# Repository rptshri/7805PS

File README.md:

View this project on [CADLAB.io](https://cadlab.io/project/2078). 

# 7805PS

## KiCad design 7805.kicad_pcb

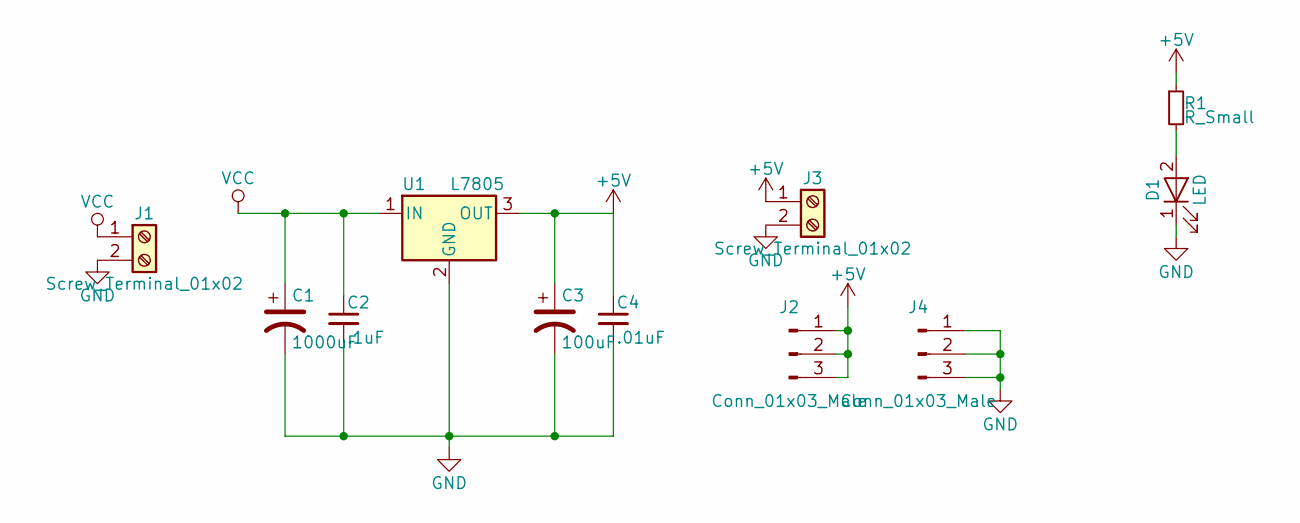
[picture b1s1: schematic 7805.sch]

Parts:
C1: 1000uF; CP_Radial_D10.0mm_P2.50mm_P5.00mm
C2: .1uF; C_Disc_D3.4mm_W2.1mm_P2.50mm
C3: 100uF; CP_Radial_D10.0mm_P5.00mm_P7.50mm
C4: .01uF; C_Disc_D3.4mm_W2.1mm_P2.50mm
D1: LED; LED_D5.0mm_FlatTop
J1, J3: Screw_Terminal_01x02; TerminalBlock_Altech_AK300-2_P5.00mm
J2, J4: Conn_01x03_Male; Pin_Header_Straight_1x03_Pitch2.54mm
R1: R_Small; R_Axial_DIN0207_L6.3mm_D2.5mm_P7.62mm_Horizontal
U1: L7805; TO-220-3_Vertical

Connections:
+5V: C3.1, C4.1, J2.1, J2.2, J2.3, J3.1, R1.1, U1.3 (OUT)
GND: C1.2, C2.2, C3.2, C4.2, D1.1 (K), J1.2, J3.2, J4.1, J4.2, J4.3, U1.2 (GND)
unnamed: D1.2 (A), R1.2
VCC: C1.1, C2.1, J1.1, U1.1 (IN)

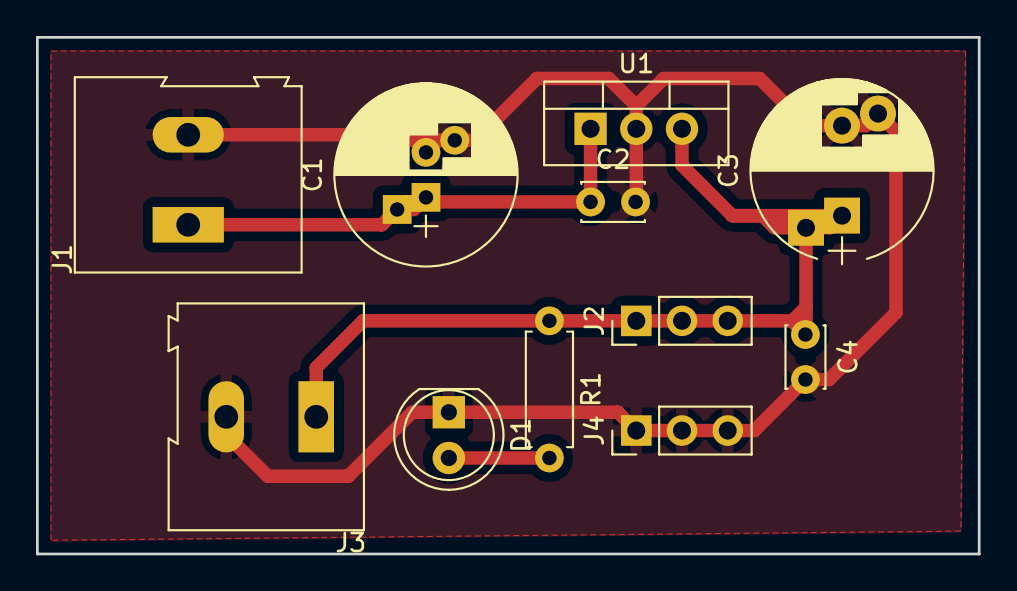
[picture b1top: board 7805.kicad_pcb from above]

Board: 2 copper layers, 52.3 x 28.7 mm, 11 parts (0 on the bottom side), 4 nets.

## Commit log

2018-10-17 7805 ps kicad files
2019-08-28 Backlink to CADLAB.io has been added.
2020-05-25 [ImgBot] Optimize images
    /7805-F.Cu.svg -- 202.53kb -> 147.39kb (27.22%)
